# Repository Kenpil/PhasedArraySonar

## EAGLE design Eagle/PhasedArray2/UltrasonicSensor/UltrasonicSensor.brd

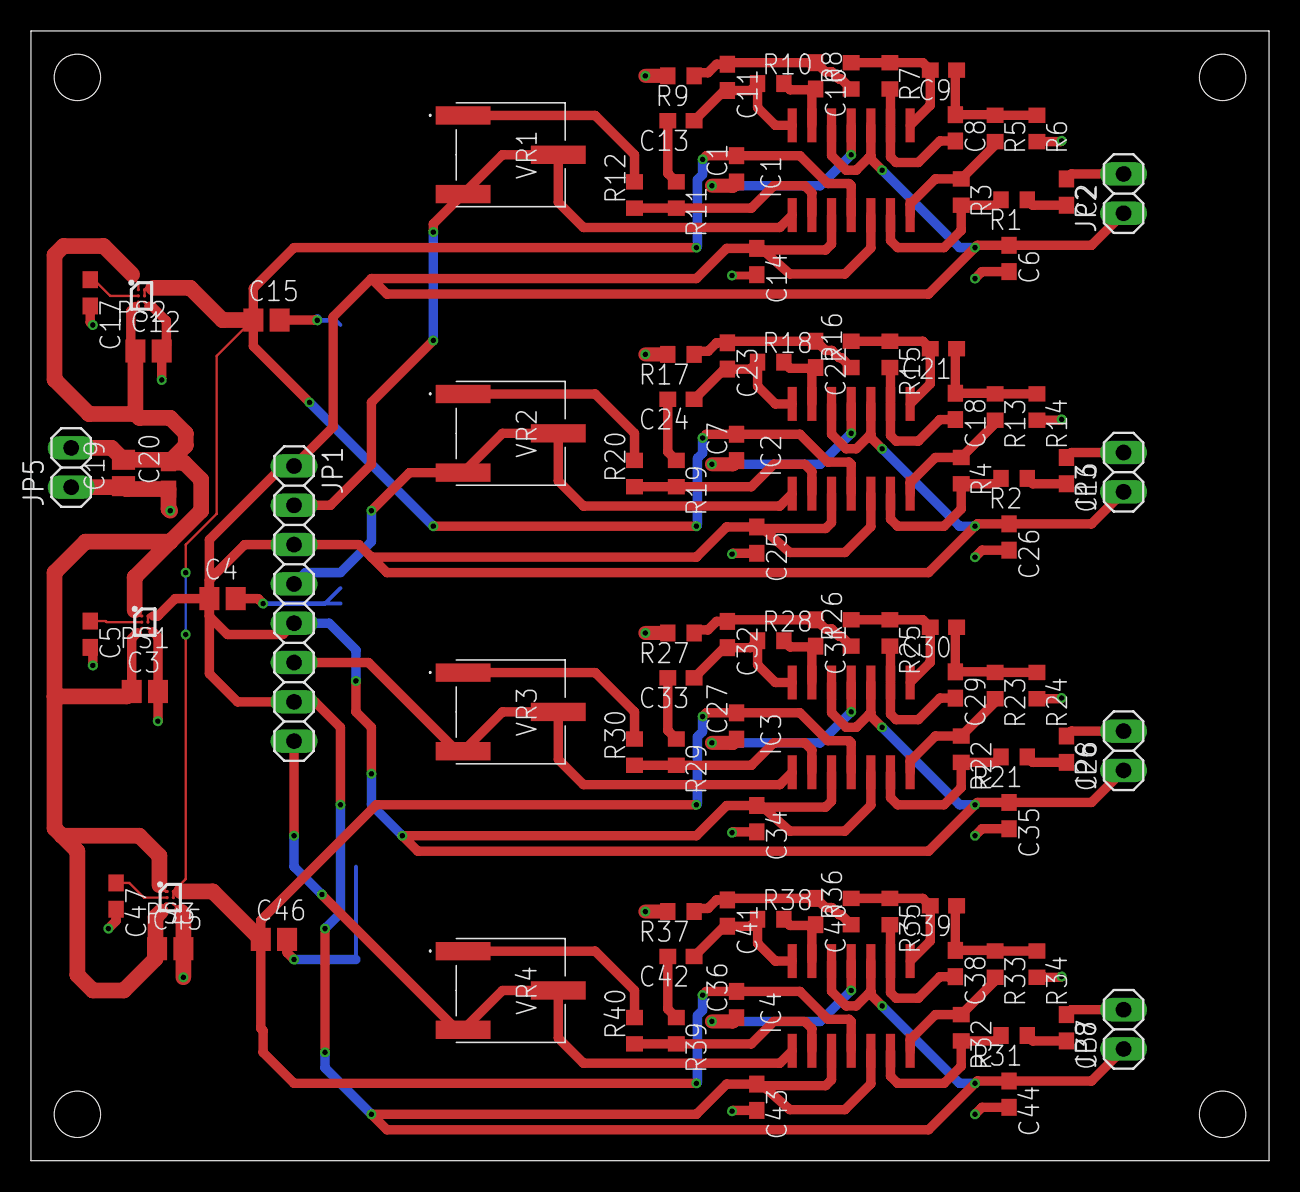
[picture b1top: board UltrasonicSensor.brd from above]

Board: 2 copper layers, 80.0 x 73.0 mm, 104 parts (0 on the bottom side), 64 nets.

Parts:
C1, C2, C6, C7, C13, C14, C16, C20, C24, C25, C26, C27, C28, C33, C34, C35, C36, C37, C42, C43, C44: 0.1u; C1608
C3, C4, C12, C15, C19, C45, C46: 10u; C2012
C5, C8, C9, C10, C11, C17, C18, C21, C22, C23, C29, C30, C31, C32, C38, C39, C40, C41, C47: 1000p; C1608
IC1, IC2, IC3, IC4: NJM2734M
JP1: 1X08
JP2, JP3, JP5, JP6, JP8: 1X02
PS1: ADP7112ACBZ-2.5-R7; BGA6C40P2X3_95X116X56
PS2, PS3: ADP7112ACBZ-5.0-R7; BGA6C40P2X3_95X116X56
R1, R2, R11, R12, R19, R20, R21, R29, R30, R31, R39, R40: 10k; R0603
R3, R4, R22, R32: 1M; R0603
R5, R13, R23, R33: 15k; R0603
R6, R14, R24, R34: 330; R0603
R7, R15, R25, R35: 39k; R0603
R8, R16, R26, R36: 18k; R0603
R9, R17, R27, R37: 390; R0603
R10, R18, R28, R38: 47k; R0603
VR1, VR2, VR3, VR4: 3361P-1-504GLF; 3361P1253GLF

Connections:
+9V: C3.1, C12.1, C19.2, C20.2, C45.1, JP5.2, PS1.A1, PS1.C1, PS2.A1, PS2.C1, PS3.A1, PS3.C1
AGND: C1.1, C4.2, C6.2, C7.1, C14.2, C15.2, C25.2, C26.2, C27.1, C34.2, C35.2, C36.1, C43.2, C44.2, C46.2, IC1.11, IC2.11, IC3.11, IC4.11, R6.2, R9.2, R14.2, R17.2, R24.2, R27.2, R34.2, R37.2
GND: C3.2, C5.2, C12.2, C17.2, C19.1, C20.1, C45.2, C47.2, JP5.1, PS1.C2, PS2.C2, PS3.C2
unnamed: C16.2, R2.1
unnamed: C13.2, R11.1
unnamed: C2.2, R1.1
unnamed: C2.1, JP2.2
unnamed: IC1.6, R1.2, R3.2
unnamed: C5.1, PS1.B1
unnamed: C8.1, C9.1, R5.1, R6.1
unnamed: C8.2, IC1.9, R7.2
unnamed: IC1.2, R11.2, R12.1
unnamed: IC1.7, R3.1, R5.2
unnamed: C9.2, IC1.8, R7.1, R8.2
unnamed: C10.1, C11.1, R8.1, R9.1
unnamed: C10.2, IC1.13, R10.2
unnamed: C11.2, C13.1, IC1.14, R10.1
unnamed: R12.2, VR1.1
unnamed: IC1.1, JP1.2, VR1.2, VR1.3
unnamed: C16.1, JP3.2
unnamed: IC2.7, R4.1, R13.2
unnamed: C18.1, C21.1, R13.1, R14.1
unnamed: IC2.6, R2.2, R4.2
unnamed: C18.2, IC2.9, R15.2
unnamed: C21.2, IC2.8, R15.1, R16.2
unnamed: C22.1, C23.1, R16.1, R17.1
unnamed: C22.2, IC2.13, R18.2
unnamed: C23.2, C24.1, IC2.14, R18.1
unnamed: C24.2, R19.1
unnamed: IC2.2, R19.2, R20.1
unnamed: R20.2, VR2.1
unnamed: IC2.1, JP1.4, VR2.2, VR2.3
unnamed: C28.2, R21.1
unnamed: C28.1, JP6.2
unnamed: IC3.7, R22.1, R23.2
unnamed: C29.1, C30.1, R23.1, R24.1
unnamed: C17.1, PS2.B1
unnamed: IC3.6, R21.2, R22.2
unnamed: C29.2, IC3.9, R25.2
unnamed: C30.2, IC3.8, R25.1, R26.2
unnamed: C31.1, C32.1, R26.1, R27.1
unnamed: C31.2, IC3.13, R28.2
unnamed: C32.2, C33.1, IC3.14, R28.1
unnamed: C33.2, R29.1
unnamed: IC3.2, R29.2, R30.1
unnamed: R30.2, VR3.1
unnamed: IC3.1, JP1.6, VR3.2, VR3.3
unnamed: C37.2, R31.1
unnamed: C37.1, JP8.2
unnamed: IC4.7, R32.1, R33.2
unnamed: C38.1, C39.1, R33.1, R34.1
unnamed: IC4.6, R31.2, R32.2
unnamed: C38.2, IC4.9, R35.2
unnamed: C39.2, IC4.8, R35.1, R36.2
unnamed: C40.1, C41.1, R36.1, R37.1
unnamed: C40.2, IC4.13, R38.2
unnamed: C41.2, C42.1, IC4.14, R38.1
unnamed: C42.2, R39.1
unnamed: IC4.2, R39.2, R40.1
unnamed: R40.2, VR4.1
unnamed: IC4.1, JP1.8, VR4.2, VR4.3
unnamed: C47.1, PS3.B1
VCC: C1.2, C7.2, C15.1, C27.2, C36.2, C46.1, IC1.4, IC2.4, IC3.4, IC4.4, PS2.A2, PS2.B2, PS3.A2, PS3.B2
VCC/2: C4.1, C6.1, C14.1, C25.1, C26.1, C34.1, C35.1, C43.1, C44.1, IC1.3, IC1.5, IC1.10, IC1.12, IC2.3, IC2.5, IC2.10, IC2.12, IC3.3, IC3.5, IC3.10, IC3.12, IC4.3, IC4.5, IC4.10, IC4.12, JP1.1, JP1.3, JP1.5, JP1.7, JP2.1, JP3.1, JP6.1, JP8.1, PS1.A2, PS1.B2

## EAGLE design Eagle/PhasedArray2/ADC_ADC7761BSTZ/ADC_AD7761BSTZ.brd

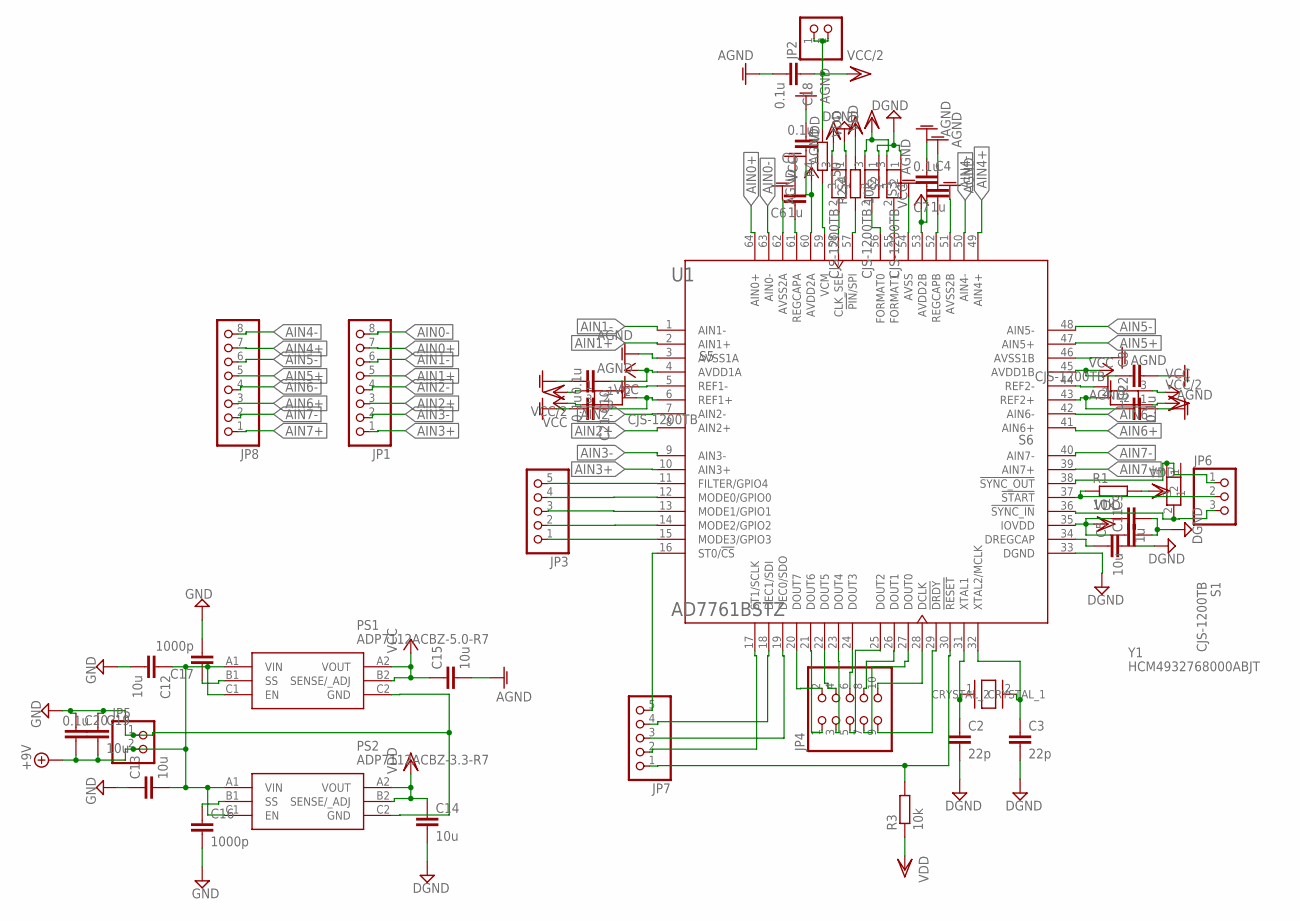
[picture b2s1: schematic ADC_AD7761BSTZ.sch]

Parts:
C1, C4, C8, C9, C10, C18, C20, C21, C22: 0.1u; C1608
C2, C3: 22p; C1608
C5, C12, C13, C14, C15, C19: 10u; C2012
C6, C7, C11: 1u; C1608
C16, C17: 1000p; C1608
JP1, JP8: PINHD-1X8; 1X08
JP2, JP5: PINHD-1X2; 1X02
JP3, JP7: PINHD-1X5; 1X05
JP4: PINHD-2X5; 2X05
JP6: PINHD-1X3; 1X03
PS1: ADP7112ACBZ-5.0-R7; BGA6C40P2X3_95X116X56
PS2: ADP7112ACBZ-3.3-R7; BGA6C40P2X3_95X116X56
R1, R2, R3: 10k; R0603
R4: 50; R0603
S1, S2, S3, S4, S5, S6: CJS-1200TB; B-TYPE
U1: AD7761BSTZ; QFP50P1200X1200X160-64N
Y1: HCM4932768000ABJT

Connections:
+9V: C12.1, C13.2, C19.2, C20.2, JP5.2, PS1.A1 (VIN), PS1.C1 (EN), PS2.A1 (VIN), PS2.C1 (EN)
AGND: C1.2, C4.1, C6.2, C7.2, C8.2, C10.2, C15.2, C18.2, C21.2, C22.2, U1.3 (AVSS1A), U1.5 (REF1-), U1.44 (REF2-), U1.46 (AVSS1B), U1.51 (AVSS2B), U1.54 (AVSS), U1.62 (AVSS2A)
AIN0+: JP1.7, U1.64 (AIN0+)
AIN0-: JP1.8, U1.63 (AIN0-)
AIN1+: JP1.5, U1.2 (AIN1+)
AIN1-: JP1.6, U1.1 (AIN1-)
AIN2+: JP1.3, U1.8 (AIN2+)
AIN2-: JP1.4, U1.7 (AIN2-)
AIN3+: JP1.1, U1.10 (AIN3+)
AIN3-: JP1.2, U1.9 (AIN3-)
AIN4+: JP8.7, U1.49 (AIN4+)
AIN4-: JP8.8, U1.50 (AIN4-)
AIN5+: JP8.5, U1.47 (AIN5+)
AIN5-: JP8.6, U1.48 (AIN5-)
AIN6+: JP8.3, U1.41 (AIN6+)
AIN6-: JP8.4, U1.42 (AIN6-)
AIN7+: JP8.1, U1.39 (AIN7+)
AIN7-: JP8.2, U1.40 (AIN7-)
DGND: C2.2, C3.2, C5.2, C9.2, C11.2, C14.2, S2.1, S3.1, S4.1, U1.33 (DGND)
GND: C12.2, C13.1, C16.2, C17.2, C19.1, C20.1, JP5.1, PS1.C2 (GND), PS2.C2 (GND)
unnamed: JP7.4, U1.18 (DEC1/SDI)
unnamed: JP7.3, U1.19 (DEC0/SDO)
unnamed: JP7.5, U1.16 (ST0/!CS)
unnamed: JP7.2, U1.17 (ST1/SCLK)
unnamed: C2.1, U1.31 (XTAL1), Y1.1 (CRYSTAL_1)
unnamed: JP6.2, R1.1, U1.37 (!START)
unnamed: C3.1, U1.32 (XTAL2/MCLK), Y1.2 (CRYSTAL_2)
unnamed: JP3.5, U1.11 (FILTER/GPIO4)
unnamed: JP3.4, U1.12 (MODE0/GPIO0)
unnamed: JP3.3, U1.13 (MODE1/GPIO1)
unnamed: JP3.2, U1.14 (MODE2/GPIO2)
unnamed: JP3.1, U1.15 (MODE3/GPIO3)
unnamed: C16.1, PS2.B1 (SS)
unnamed: C7.1, U1.52 (REGCAPB)
unnamed: JP4.2, U1.20 (DOUT7)
unnamed: JP4.1, U1.21 (DOUT6)
unnamed: JP4.4, U1.22 (DOUT5)
unnamed: JP4.3, U1.23 (DOUT4)
unnamed: JP4.6, U1.24 (DOUT3)
unnamed: JP4.5, U1.25 (DOUT2)
unnamed: JP4.8, U1.26 (DOUT1)
unnamed: JP4.7, U1.27 (DOUT0)
unnamed: JP4.10, U1.28 (DCLK)
unnamed: JP4.9, U1.29 (!DRDY)
unnamed: C5.1, U1.34 (DREGCAP)
unnamed: R2.1, U1.57 (!PIN!/SPI)
unnamed: C6.1, U1.61 (REGCAPA)
unnamed: JP6.3, S1.2, U1.36 (!SYNC_IN)
unnamed: S4.2, U1.58 (CLK_SEL)
unnamed: JP6.1, S1.3, U1.38 (!SYNC_OUT)
unnamed: S2.2, U1.56 (FORMAT0)
unnamed: S3.2, U1.55 (FORMAT1)
unnamed: R4.1, U1.59 (VCM)
unnamed: C17.1, PS1.B1 (SS)
unnamed: JP7.1, R3.2, U1.30 (!RESET)
unnamed: C22.1, S6.2, U1.43 (REF2+)
unnamed: C21.1, S5.2, U1.6 (REF1+)
VCC: C1.1, C4.2, C8.1, C10.1, C15.1, PS1.A2 (VOUT), PS1.B2 (SENSE/_ADJ), S5.3, S6.3, U1.4 (AVDD1A), U1.45 (AVDD1B), U1.53 (AVDD2B), U1.60 (AVDD2A)
VCC/2: C18.1, JP2.1, JP2.2, R4.2, S5.1, S6.1
VDD: C9.1, C11.1, C14.1, PS2.A2 (VOUT), PS2.B2 (SENSE/_ADJ), R1.2, R2.2, R3.1, S2.3, S3.3, S4.3, U1.35 (IOVDD)

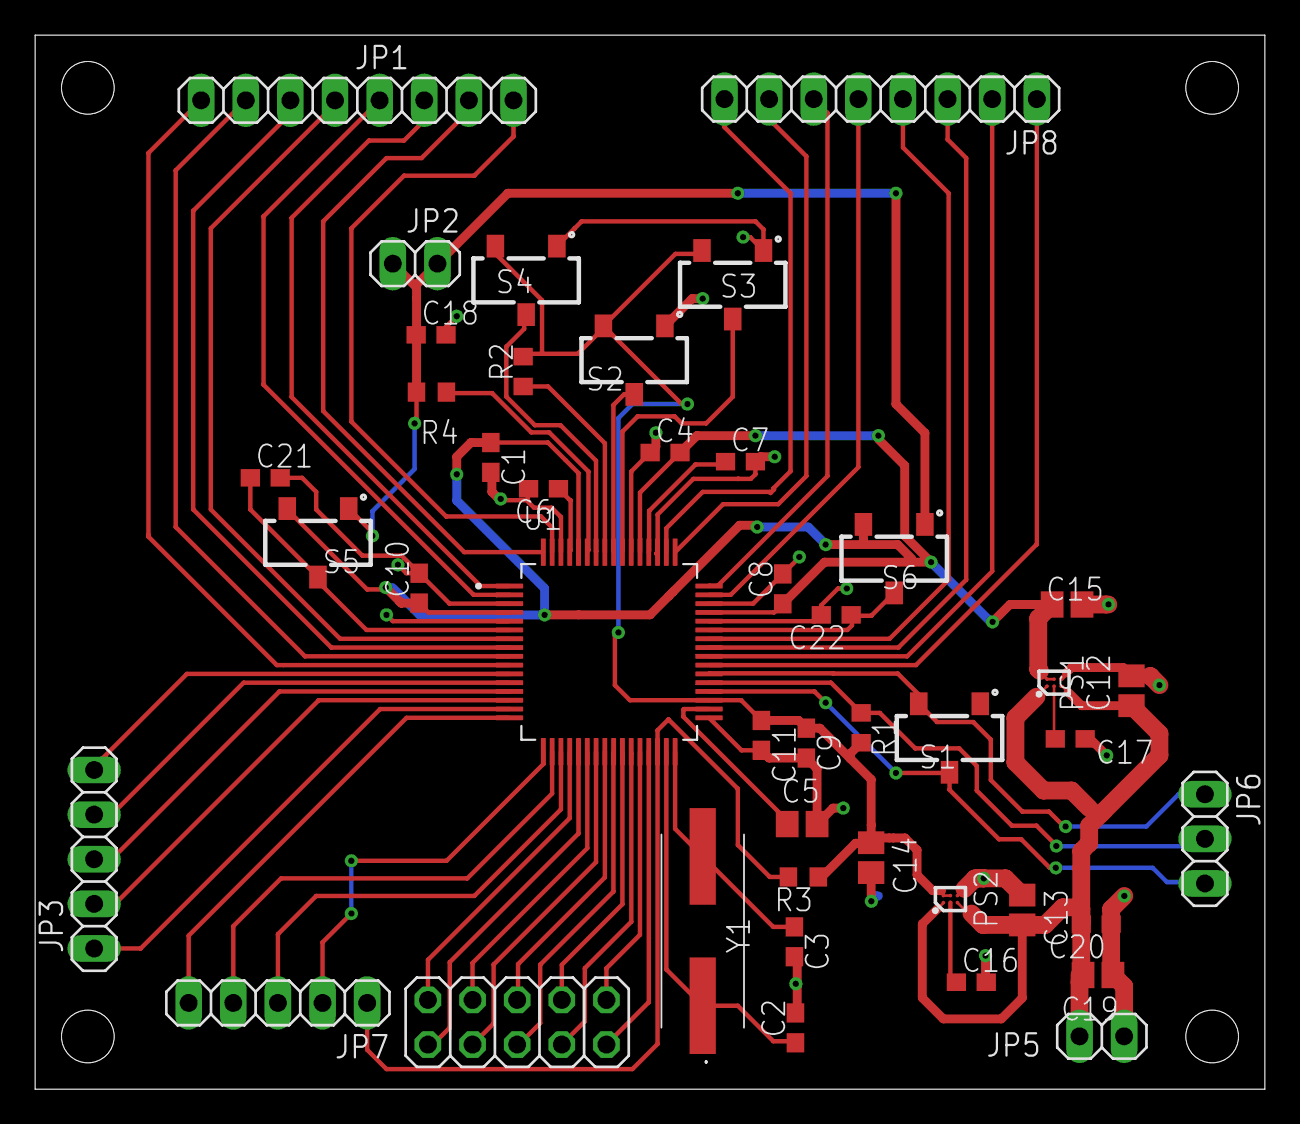
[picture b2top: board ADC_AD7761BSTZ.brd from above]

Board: 2 copper layers, 70.0 x 60.0 mm, 44 parts (0 on the bottom side), 60 nets.

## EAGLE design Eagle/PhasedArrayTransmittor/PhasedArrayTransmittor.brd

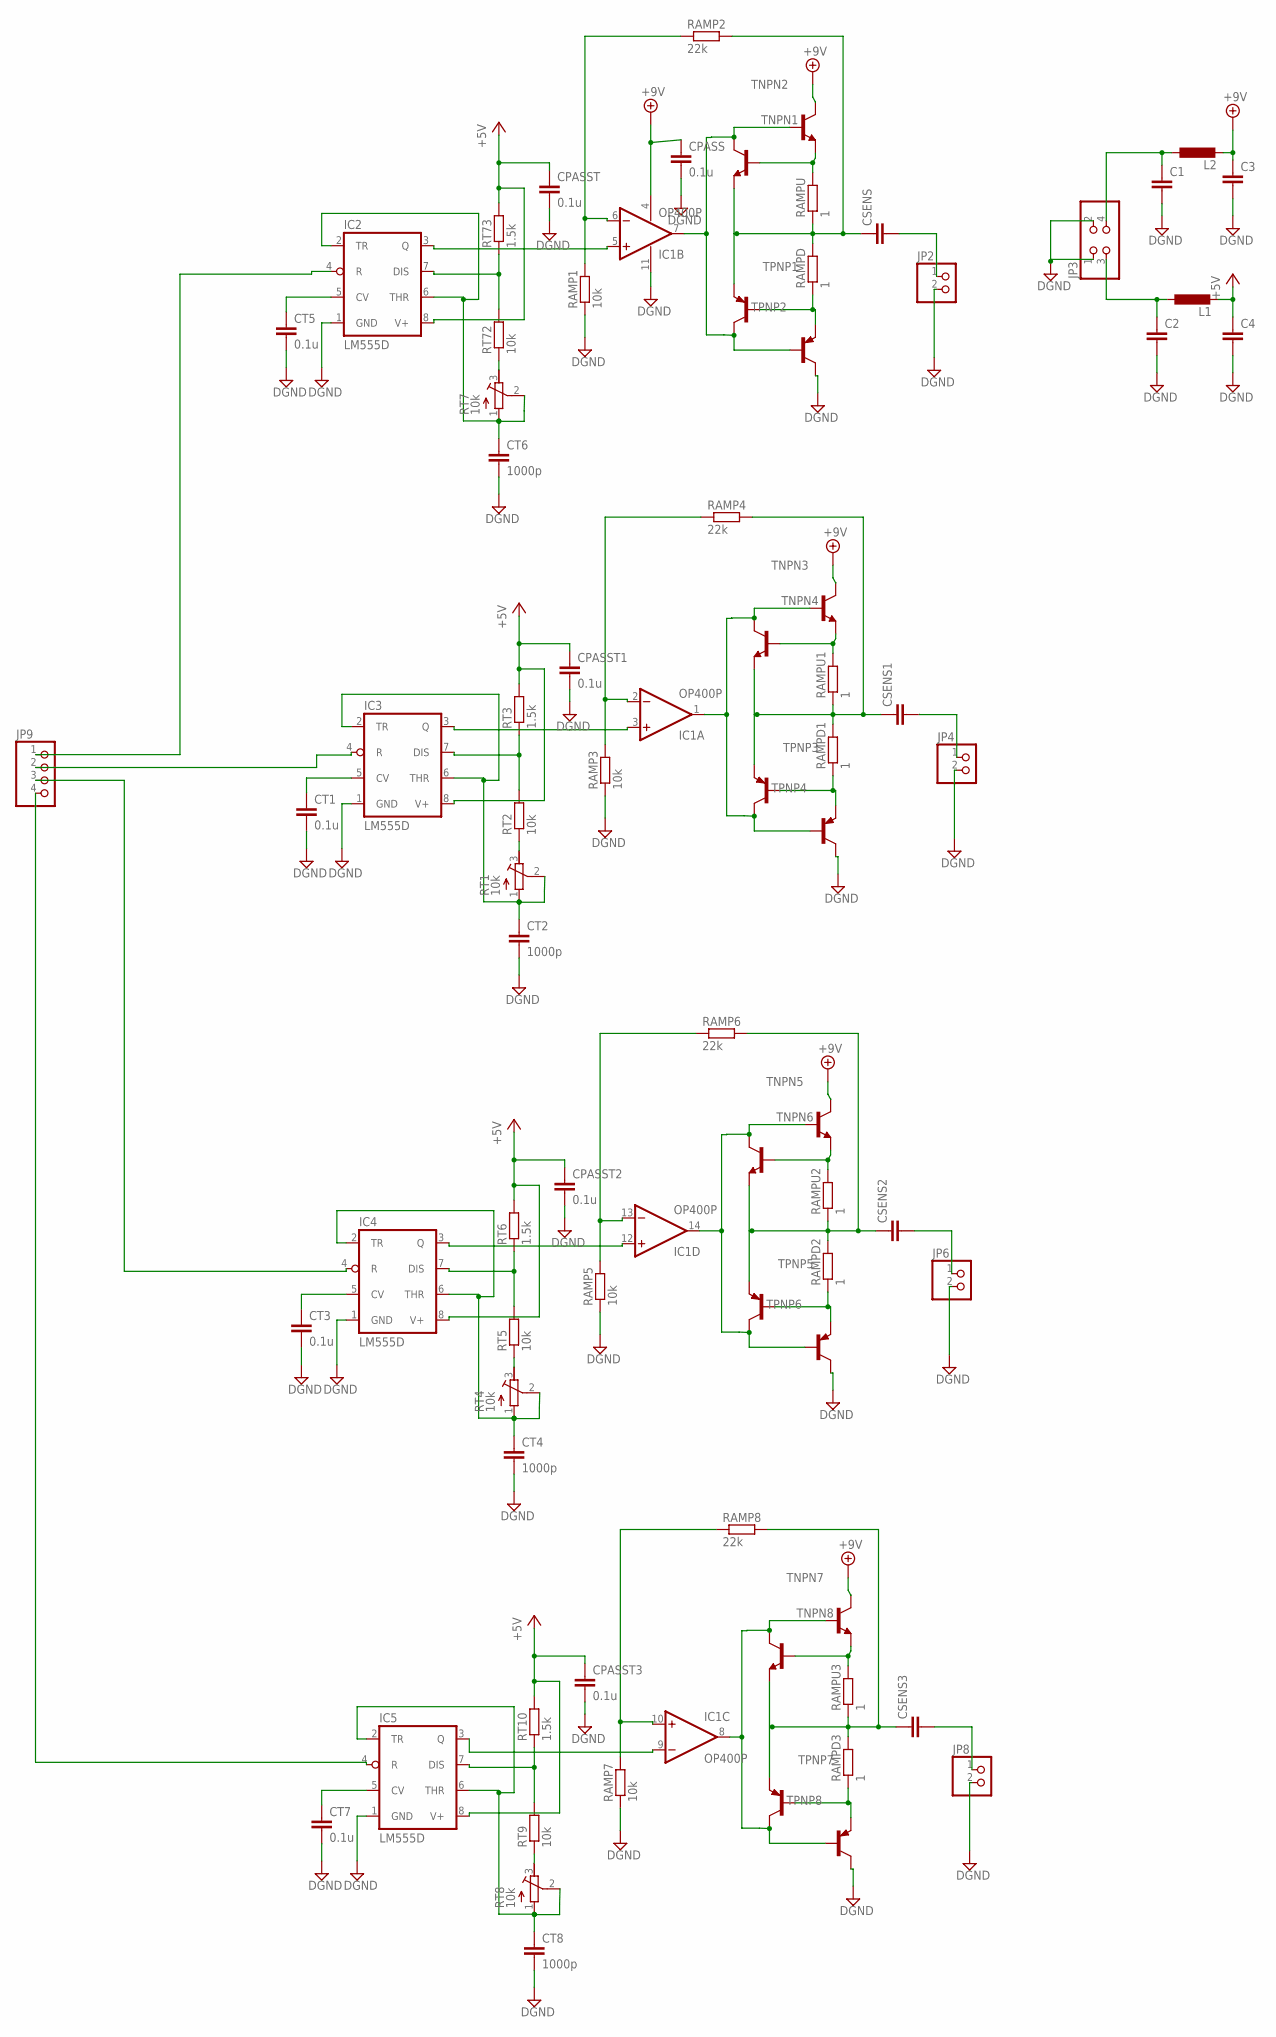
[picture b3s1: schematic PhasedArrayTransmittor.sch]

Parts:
C1, C2, C3, C4: C-EU025-024X044; C025-024X044
CPASS: 0.1u; C0603K
CPASST, CPASST1, CPASST2, CPASST3: 0.1u; C025-024X044
CSENS, CSENS1, CSENS2, CSENS3: C-EUC0603K; C0603K
CT1, CT3, CT5, CT7: 0.1u; C025-024X044
CT2, CT4, CT6, CT8: 1000p; C025-024X044
IC1: OP400P; DIL14
IC2, IC3, IC4, IC5: LM555D; SO08
JP2, JP4, JP6, JP8: PINHD-1X2; 1X02
JP3: PINHD-2X2; 2X02
JP9: PINHD-1X4; 1X04
L1, L2: L-EU0207/7; 0207/7
RAMP1, RAMP3, RAMP5, RAMP7: 10k; R0603
RAMP2, RAMP4, RAMP6, RAMP8: 22k; R0603
RAMPD, RAMPD1, RAMPD2, RAMPD3: 1; R0603
RAMPU, RAMPU1, RAMPU2, RAMPU3: 1; R0603
RT1, RT4, RT7, RT8: 10k; RTRIM74W
RT2, RT5, RT9, RT72: 10k; R0603
RT3, RT6, RT10, RT73: 1.5k; R0603
TNPN1, TNPN2, TNPN3, TNPN4, TNPN5, TNPN6, TNPN7, TNPN8: BC817-16-NPN-SOT23-BEC; SOT23-BEC
TPNP1, TPNP2, TPNP3, TPNP4, TPNP5, TPNP6, TPNP7, TPNP8: BC807-16-PNP-SOT23-BEC; SOT23-BEC

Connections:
+5V: C4.1, CPASST.1, CPASST1.1, CPASST2.1, CPASST3.1, IC2.8 (V+), IC3.8 (V+), IC4.8 (V+), IC5.8 (V+), L1.2, RT3.2, RT6.2, RT10.2, RT73.2
+9V: C3.1, CPASS.1, IC1.4 (V+), L2.2, TNPN2.C, TNPN3.C, TNPN5.C, TNPN7.C
DGND: C1.2, C2.2, C3.2, C4.2, CPASS.2, CPASST.2, CPASST1.2, CPASST2.2, CPASST3.2, CT1.2, CT2.2, CT3.2, CT4.2, CT5.2, CT6.2, CT7.2, CT8.2, IC1.11 (V-), IC2.1 (GND), IC3.1 (GND), IC4.1 (GND), IC5.1 (GND), JP2.2, JP3.1, JP3.2, JP4.2, JP6.2, JP8.2, RAMP1.1, RAMP3.1, RAMP5.1, RAMP7.1, TPNP2.C, TPNP4.C, TPNP6.C, TPNP8.C
unnamed: RT1.3 (E), RT2.1
unnamed: CT5.1, IC2.5 (CV)
unnamed: RT7.3 (E), RT72.1
unnamed: IC1.6 (-IN), RAMP1.2, RAMP2.1
unnamed: IC2.7 (DIS), RT72.2, RT73.1
unnamed: IC5.4 (R), JP9.4
unnamed: IC1.7 (OUT), TNPN1.C, TNPN2.B, TPNP1.C, TPNP2.B
unnamed: CT6.1, IC2.2 (TR), IC2.6 (THR), RT7.1 (A), RT7.2 (S)
unnamed: IC3.7 (DIS), RT2.2, RT3.1
unnamed: RAMPD.1, TPNP1.B, TPNP2.E
unnamed: IC4.4 (R), JP9.3
unnamed: CT2.1, IC3.2 (TR), IC3.6 (THR), RT1.1 (A), RT1.2 (S)
unnamed: RAMPU.2, TNPN1.B, TNPN2.E
unnamed: CSENS.1, RAMP2.2, RAMPD.2, RAMPU.1, TNPN1.E, TPNP1.E
unnamed: IC1.2 (-IN), RAMP3.2, RAMP4.1
unnamed: CSENS.2, JP2.1
unnamed: RAMPU1.2, TNPN3.E, TNPN4.B
unnamed: IC1.1 (OUT), TNPN3.B, TNPN4.C, TPNP3.C, TPNP4.B
unnamed: RAMPD1.1, TPNP3.B, TPNP4.E
unnamed: CSENS1.1, RAMP4.2, RAMPD1.2, RAMPU1.1, TNPN4.E, TPNP3.E
unnamed: CSENS1.2, JP4.1
unnamed: CT1.1, IC3.5 (CV)
unnamed: RT4.3 (E), RT5.1
unnamed: IC4.7 (DIS), RT5.2, RT6.1
unnamed: IC3.4 (R), JP9.2
unnamed: CT4.1, IC4.2 (TR), IC4.6 (THR), RT4.1 (A), RT4.2 (S)
unnamed: IC1.13 (-IN), RAMP5.2, RAMP6.1
unnamed: RAMPU2.2, TNPN5.E, TNPN6.B
unnamed: IC1.14 (OUT), TNPN5.B, TNPN6.C, TPNP5.C, TPNP6.B
unnamed: RAMPD2.1, TPNP5.B, TPNP6.E
unnamed: CSENS2.1, RAMP6.2, RAMPD2.2, RAMPU2.1, TNPN6.E, TPNP5.E
unnamed: CSENS2.2, JP6.1
unnamed: CT3.1, IC4.5 (CV)
unnamed: RT8.3 (E), RT9.1
unnamed: IC5.7 (DIS), RT9.2, RT10.1
unnamed: IC2.4 (R), JP9.1
unnamed: CT8.1, IC5.2 (TR), IC5.6 (THR), RT8.1 (A), RT8.2 (S)
unnamed: IC1.10 (+IN), RAMP7.2, RAMP8.1
unnamed: RAMPU3.2, TNPN7.E, TNPN8.B
unnamed: IC1.8 (OUT), TNPN7.B, TNPN8.C, TPNP7.C, TPNP8.B
unnamed: RAMPD3.1, TPNP7.B, TPNP8.E
unnamed: CSENS3.1, RAMP8.2, RAMPD3.2, RAMPU3.1, TNPN8.E, TPNP7.E
unnamed: CSENS3.2, JP8.1
unnamed: CT7.1, IC5.5 (CV)
unnamed: IC1.5 (+IN), IC2.3 (Q)
unnamed: IC1.3 (+IN), IC3.3 (Q)
unnamed: IC1.12 (+IN), IC4.3 (Q)
unnamed: IC1.9 (-IN), IC5.3 (Q)
unnamed: C2.1, JP3.3, L1.1
unnamed: C1.1, JP3.4, L2.1

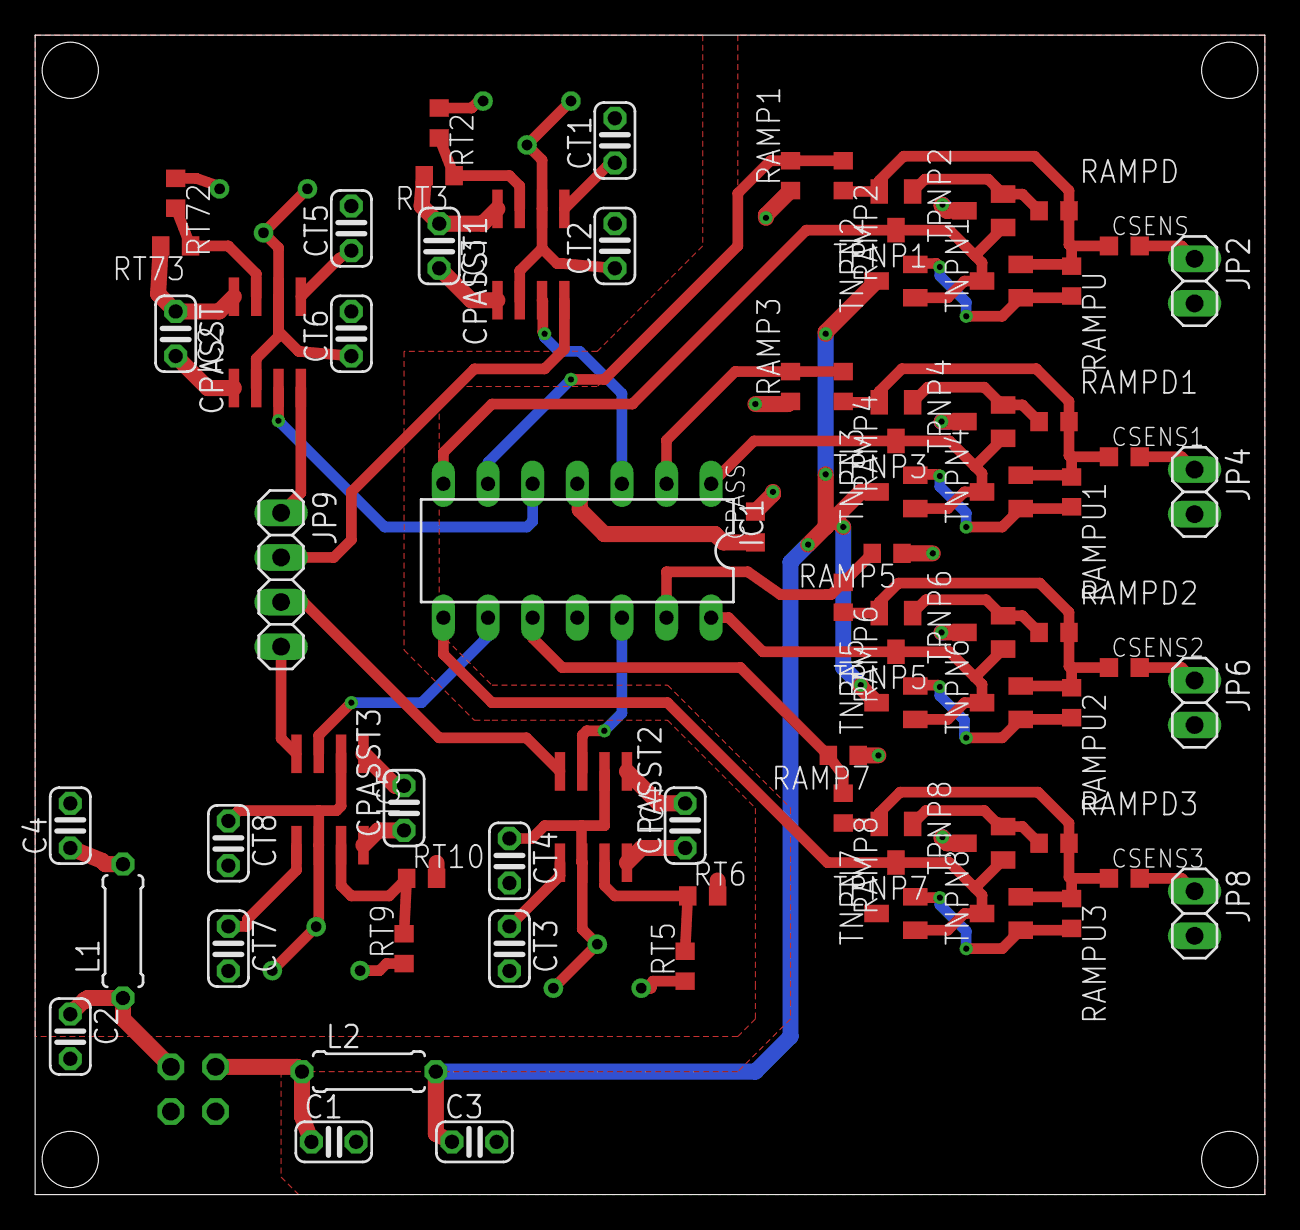
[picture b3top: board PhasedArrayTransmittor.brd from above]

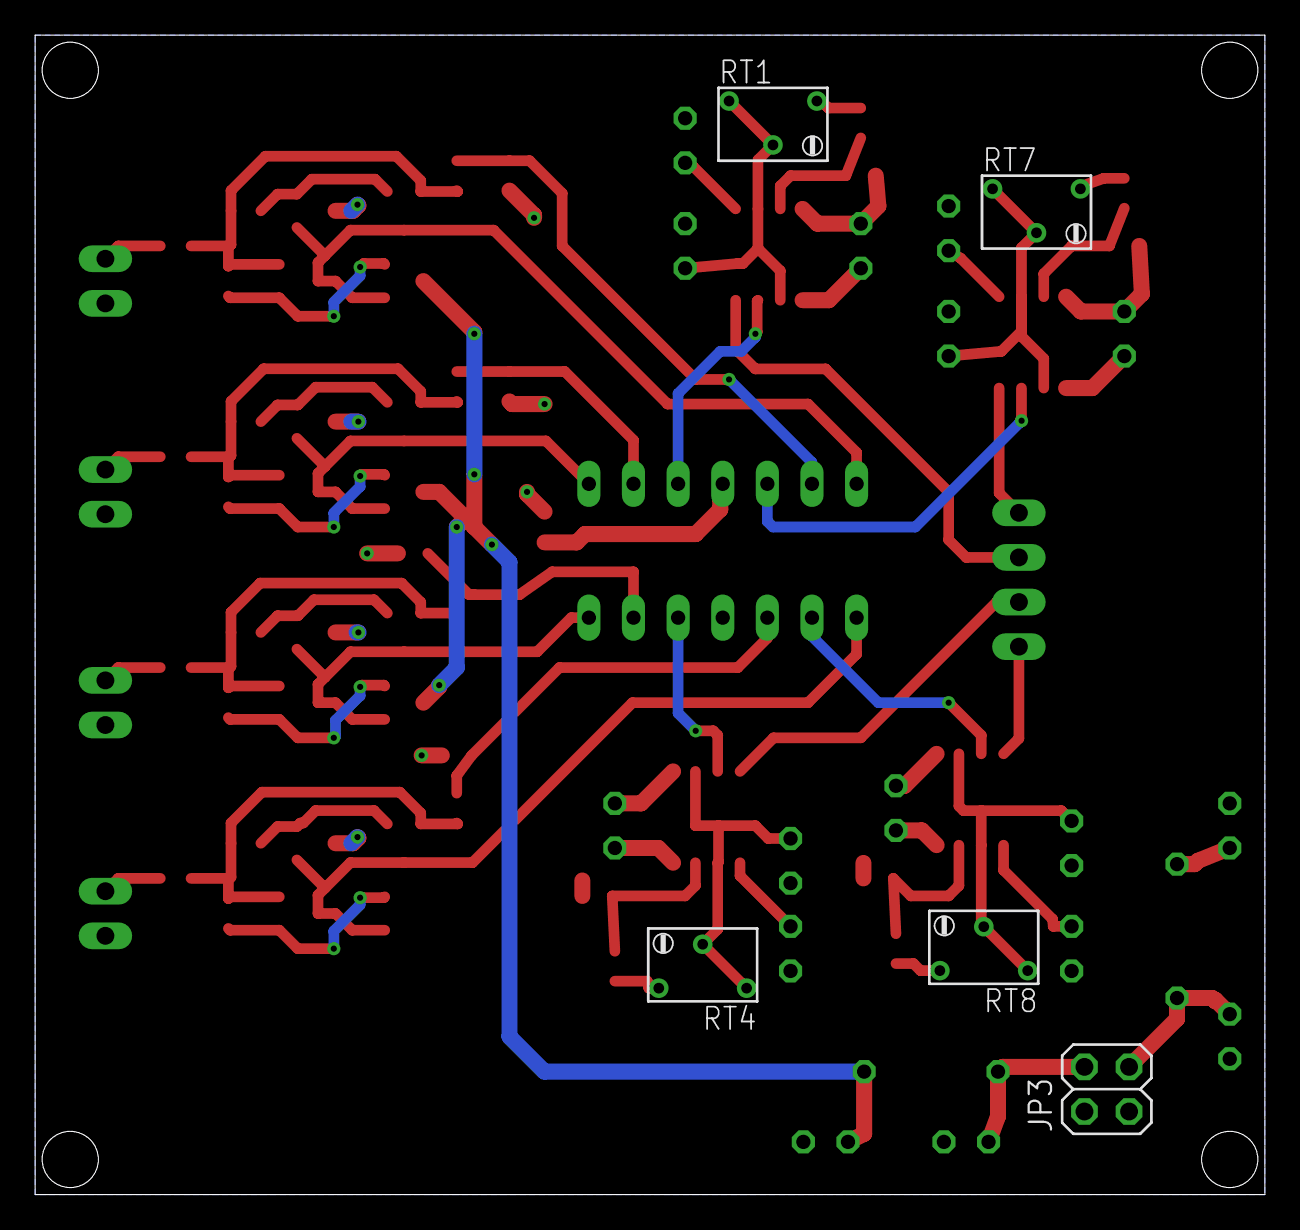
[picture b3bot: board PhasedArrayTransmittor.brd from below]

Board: 2 copper layers, 70.0 x 66.0 mm, 78 parts (5 on the bottom side), 53 nets.

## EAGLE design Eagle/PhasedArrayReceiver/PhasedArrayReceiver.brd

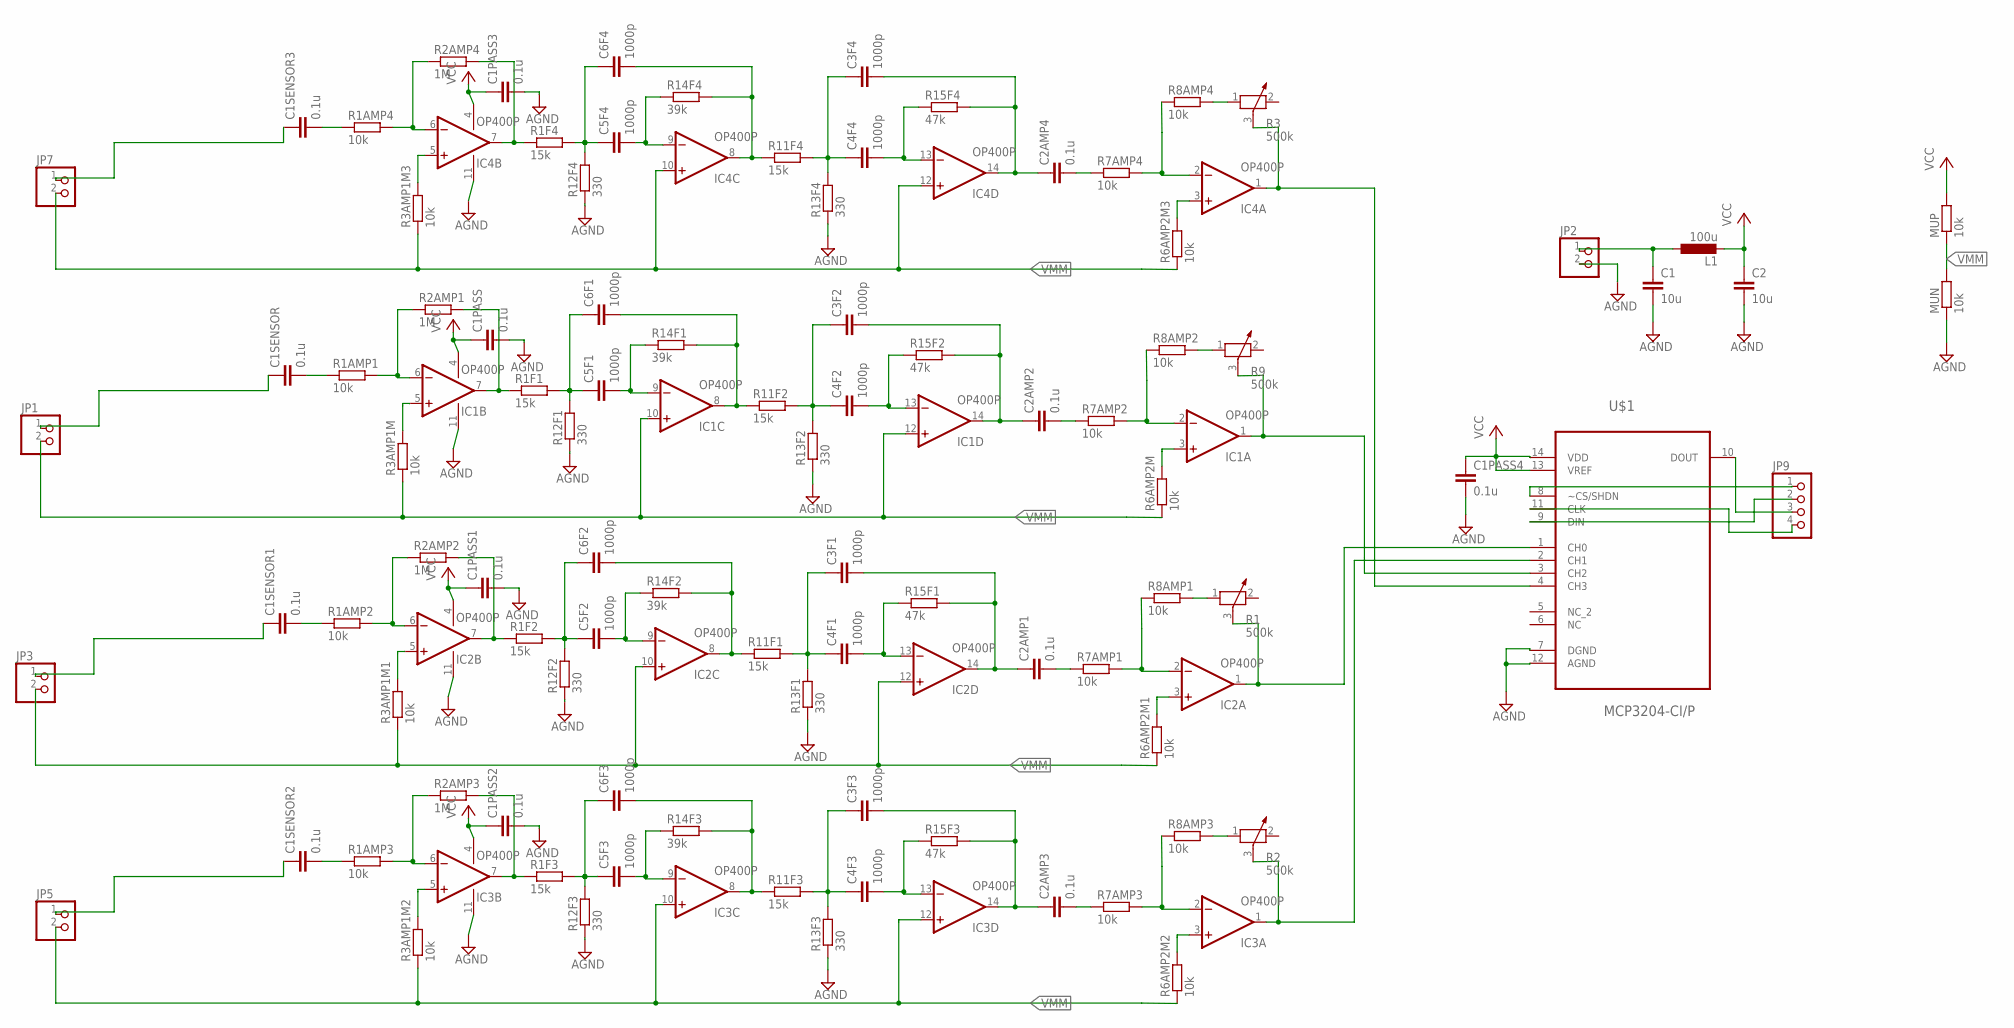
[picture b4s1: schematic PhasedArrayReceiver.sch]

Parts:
C1, C2: 10u; C025-024X044
C1PASS, C1PASS1, C1PASS2, C1PASS3, C1PASS4: 0.1u; C025-024X044
C1SENSOR, C1SENSOR1, C1SENSOR2, C1SENSOR3, C2AMP1, C2AMP2, C2AMP3, C2AMP4: 0.1u; C0603K
C3F1, C3F2, C3F3, C3F4, C4F1, C4F2, C4F3, C4F4, C5F1, C5F2, C5F3, C5F4, C6F1, C6F2, C6F3, C6F4: 1000p; C0603K
IC1, IC2, IC3, IC4: OP400P; DIL14
JP1, JP2, JP3, JP5, JP7: PINHD-1X2; 1X02
JP9: PINHD-1X4; 1X04
L1: 100u; 0207/7
MUN: 10k; 0207/7
MUP: 10k; 0207/7
R1, R2, R3, R9: 500k; PT-10
R1AMP1, R1AMP2, R1AMP3, R1AMP4, R3AMP1M, R3AMP1M1, R3AMP1M2, R3AMP1M3, R6AMP2M, R6AMP2M1, R6AMP2M2, R6AMP2M3, R7AMP1, R7AMP2, R7AMP3, R7AMP4, R8AMP1, R8AMP2, R8AMP3, R8AMP4: 10k; R0603
R1F1, R1F2, R1F3, R1F4: 15k; 0207/7
R2AMP1, R2AMP2, R2AMP3, R2AMP4: 1M; R0603
R11F1, R11F2, R11F3, R11F4: 15k; R0603
R12F1, R12F2, R12F3, R12F4, R13F1, R13F2, R13F3, R13F4: 330; R0603
R14F1, R14F2, R14F3, R14F4: 39k; 0207/7
R15F1, R15F2, R15F3, R15F4: 47k; 0207/7
U$1: MCP3204-CI/P; DIP254P762X432-14

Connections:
AGND: C1.2, C1PASS.2, C1PASS1.2, C1PASS2.2, C1PASS3.2, C1PASS4.2, C2.2, IC1.11 (V-), IC2.11 (V-), IC3.11 (V-), IC4.11 (V-), JP2.2, MUN.1, R12F1.1, R12F2.1, R12F3.1, R12F4.1, R13F1.1, R13F2.1, R13F3.1, R13F4.1, U$1.7 (DGND), U$1.12 (AGND)
unnamed: IC1.6 (-IN), R1AMP1.2, R2AMP1.1
unnamed: IC1.5 (+IN), R3AMP1M.2
unnamed: IC1.7 (OUT), R1F1.1, R2AMP1.2
unnamed: IC1.2 (-IN), R7AMP2.2, R8AMP2.1
unnamed: IC2.6 (-IN), R1AMP2.2, R2AMP2.1
unnamed: C1SENSOR.1, JP1.1
unnamed: IC1.3 (+IN), R6AMP2M.2
unnamed: C1SENSOR.2, R1AMP1.1
unnamed: C2AMP2.2, R7AMP2.1
unnamed: R8AMP2.2, R9.1
unnamed: IC1.1 (OUT), R9.3, U$1.3 (CH2)
unnamed: C2AMP2.1, C3F2.2, IC1.14 (OUT), R15F2.2
unnamed: C5F1.2, IC1.9 (-IN), R14F1.1
unnamed: C4F2.2, IC1.13 (-IN), R15F2.1
unnamed: C3F2.1, C4F2.1, R11F2.2, R13F2.2
unnamed: C6F1.2, IC1.8 (OUT), R11F2.1, R14F1.2
unnamed: C5F1.1, C6F1.1, R1F1.2, R12F1.2
unnamed: IC2.7 (OUT), R1F2.1, R2AMP2.2
unnamed: IC2.2 (-IN), R7AMP1.2, R8AMP1.1
unnamed: IC2.3 (+IN), R6AMP2M1.2
unnamed: C1SENSOR1.2, R1AMP2.1
unnamed: C2AMP1.2, R7AMP1.1
unnamed: R1.1, R8AMP1.2
unnamed: C2AMP1.1, C3F1.2, IC2.14 (OUT), R15F1.2
unnamed: C5F2.2, IC2.9 (-IN), R14F2.1
unnamed: C4F1.2, IC2.13 (-IN), R15F1.1
unnamed: C3F1.1, C4F1.1, R11F1.2, R13F1.2
unnamed: C6F2.2, IC2.8 (OUT), R11F1.1, R14F2.2
unnamed: C5F2.1, C6F2.1, R1F2.2, R12F2.2
unnamed: IC2.5 (+IN), R3AMP1M1.2
unnamed: C1SENSOR1.1, JP3.1
unnamed: IC2.1 (OUT), R1.3, U$1.1 (CH0)
unnamed: IC3.6 (-IN), R1AMP3.2, R2AMP3.1
unnamed: IC3.7 (OUT), R1F3.1, R2AMP3.2
unnamed: IC3.2 (-IN), R7AMP3.2, R8AMP3.1
unnamed: IC3.3 (+IN), R6AMP2M2.2
unnamed: C1SENSOR2.2, R1AMP3.1
unnamed: C2AMP3.2, R7AMP3.1
unnamed: R2.1, R8AMP3.2
unnamed: C2AMP3.1, C3F3.2, IC3.14 (OUT), R15F3.2
unnamed: C5F3.2, IC3.9 (-IN), R14F3.1
unnamed: C4F3.2, IC3.13 (-IN), R15F3.1
unnamed: C3F3.1, C4F3.1, R11F3.2, R13F3.2
unnamed: C6F3.2, IC3.8 (OUT), R11F3.1, R14F3.2
unnamed: C5F3.1, C6F3.1, R1F3.2, R12F3.2
unnamed: IC3.5 (+IN), R3AMP1M2.2
unnamed: C1SENSOR2.1, JP5.1
unnamed: IC3.1 (OUT), R2.3, U$1.2 (CH1)
unnamed: IC4.6 (-IN), R1AMP4.2, R2AMP4.1
unnamed: IC4.7 (OUT), R1F4.1, R2AMP4.2
unnamed: IC4.2 (-IN), R7AMP4.2, R8AMP4.1
unnamed: IC4.3 (+IN), R6AMP2M3.2
unnamed: C1SENSOR3.2, R1AMP4.1
unnamed: C2AMP4.2, R7AMP4.1
unnamed: R3.1, R8AMP4.2
unnamed: C2AMP4.1, C3F4.2, IC4.14 (OUT), R15F4.2
unnamed: C5F4.2, IC4.9 (-IN), R14F4.1
unnamed: C4F4.2, IC4.13 (-IN), R15F4.1
unnamed: C3F4.1, C4F4.1, R11F4.2, R13F4.2
unnamed: C6F4.2, IC4.8 (OUT), R11F4.1, R14F4.2
unnamed: C5F4.1, C6F4.1, R1F4.2, R12F4.2
unnamed: IC4.5 (+IN), R3AMP1M3.2
unnamed: C1SENSOR3.1, JP7.1
unnamed: IC4.1 (OUT), R3.3, U$1.4 (CH3)
unnamed: JP9.1, U$1.8 (~CS/SHDN)
unnamed: JP9.2, U$1.9 (DIN)
unnamed: JP9.3, U$1.10 (DOUT)
unnamed: JP9.4, U$1.11 (CLK)
unnamed: C1.1, JP2.1, L1.1
VCC: C1PASS.1, C1PASS1.1, C1PASS2.1, C1PASS3.1, C1PASS4.1, C2.1, IC1.4 (V+), IC2.4 (V+), IC3.4 (V+), IC4.4 (V+), L1.2, MUP.2, U$1.13 (VREF), U$1.14 (VDD)
VMM: IC1.10 (+IN), IC1.12 (+IN), IC2.10 (+IN), IC2.12 (+IN), IC3.10 (+IN), IC3.12 (+IN), IC4.10 (+IN), IC4.12 (+IN), JP1.2, JP3.2, JP5.2, JP7.2, MUN.2, MUP.1, R3AMP1M.1, R3AMP1M1.1, R3AMP1M2.1, R3AMP1M3.1, R6AMP2M.1, R6AMP2M1.1, R6AMP2M2.1, R6AMP2M3.1

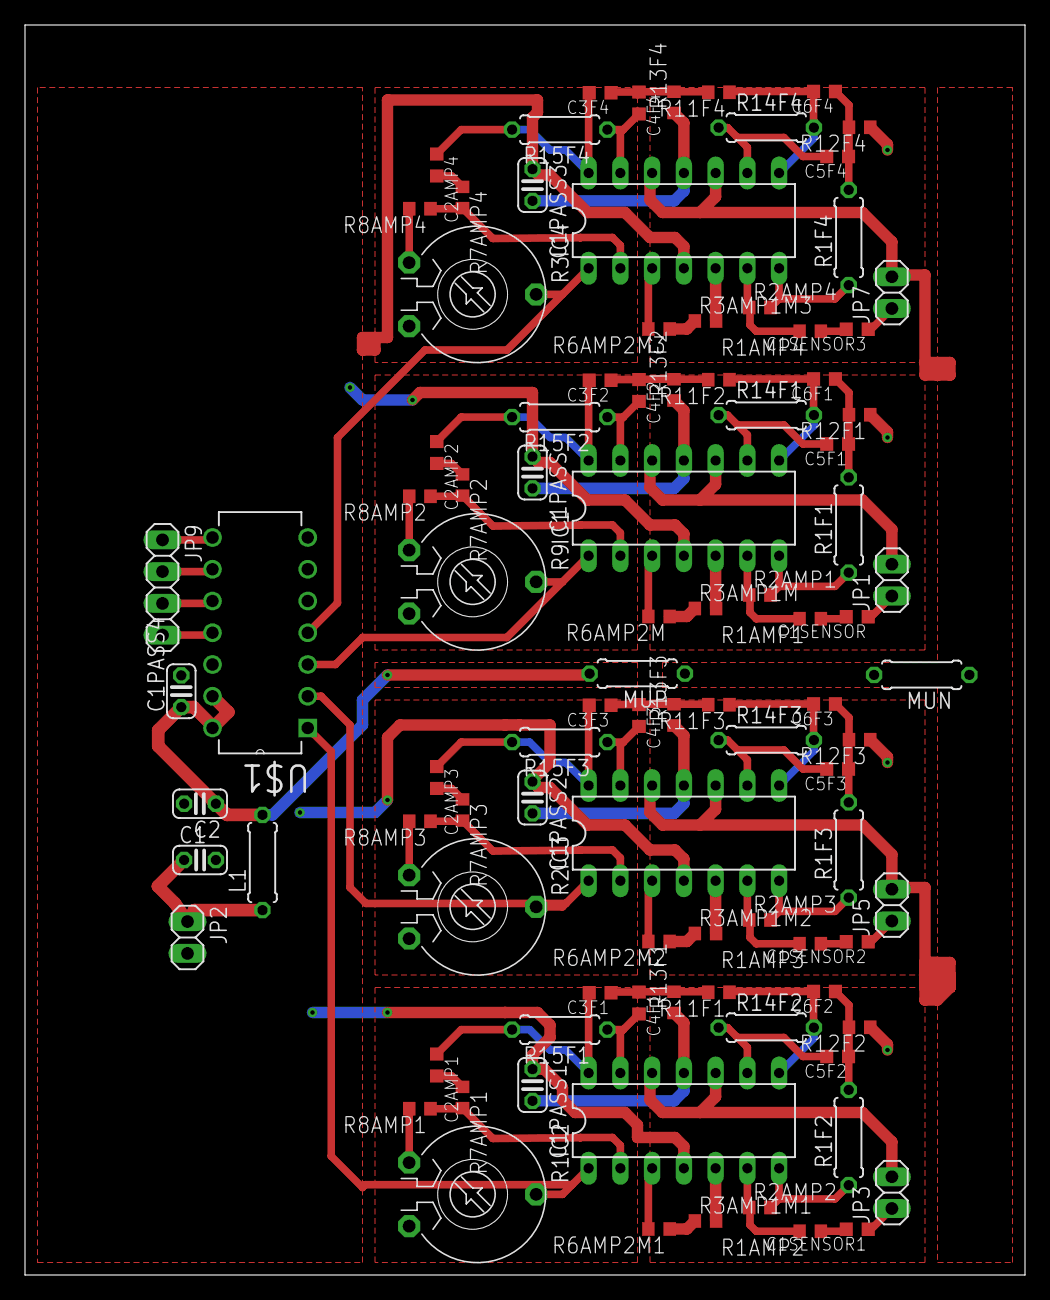
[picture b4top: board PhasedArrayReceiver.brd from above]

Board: 2 copper layers, 80.0 x 100.0 mm, 97 parts (0 on the bottom side), 72 nets.

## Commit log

2019-07-14 Create directivity(ok1).mlx
    https://www.jstage.jst.go.jp/article/jasj/74/6/74_345/_pdf/-char/en
    『パラメトリックアレイとその特徴』日本音響学会誌74巻6号（2018），pp. 345–352, 鎌倉友男，酒井新一
    ピストン音源の指向性を求めた
2019-07-14 Update directivity(ok1).mlx
    アコースティックイメージング
    ベッセル関数
    20log10(P/P0)
2020-03-06 Rename UltrasonicSensorArray.brd to UltrasonicSensorArray1.brd
2020-03-06 Rename UltrasonicSensorArray.sch to UltrasonicSensorArray1.sch
2020-03-07 Rename UltrasonicSensorArray.brd to UltrasonicSensorArray2.brd
2020-03-07 Rename UltrasonicSensorArray.sch to UltrasonicSensorArray2.sch
2020-03-07 Rename UltrasonicSensorArray2.brd to UltrasonicSensorArray3.brd
2020-03-07 Rename UltrasonicSensorArray.sch to UltrasonicSensorArray3.sch
2020-03-08 Rename PhasedArrayReceiver.brd to PhasedArrayReceiver1.brd
2020-03-08 Rename PhasedArrayReceiver.sch to PhasedArrayReceiver1.sch
